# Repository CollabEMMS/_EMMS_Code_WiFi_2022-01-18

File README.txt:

WiFI Module
@author: Zach Holsinger
@editor: Joe Wambach

last edit date: 4/4/2019

v1.0

Version History:
	v1.0: 	Initial Prototype
	v1.1:	Changed Voltage Regulator SCH symbol and footprint
		Changed SPI connector and PICKit connector symbols and footprints

Needs To Be Changed:
	- Pad Size?
	- General Drill Size
	- Need to change holes for 3.3v regulator because holes are too small
		DONE
	- Add silkscreen for DIP switch positions
	- Add silkscreen for SPI header orientation
		DONE
	- Change SCH symbol for headers and connectors
		DONE
	- Add Silkscreen labels to new header footprints
		DONE
	- Add 12V pin on SPI
		DONE

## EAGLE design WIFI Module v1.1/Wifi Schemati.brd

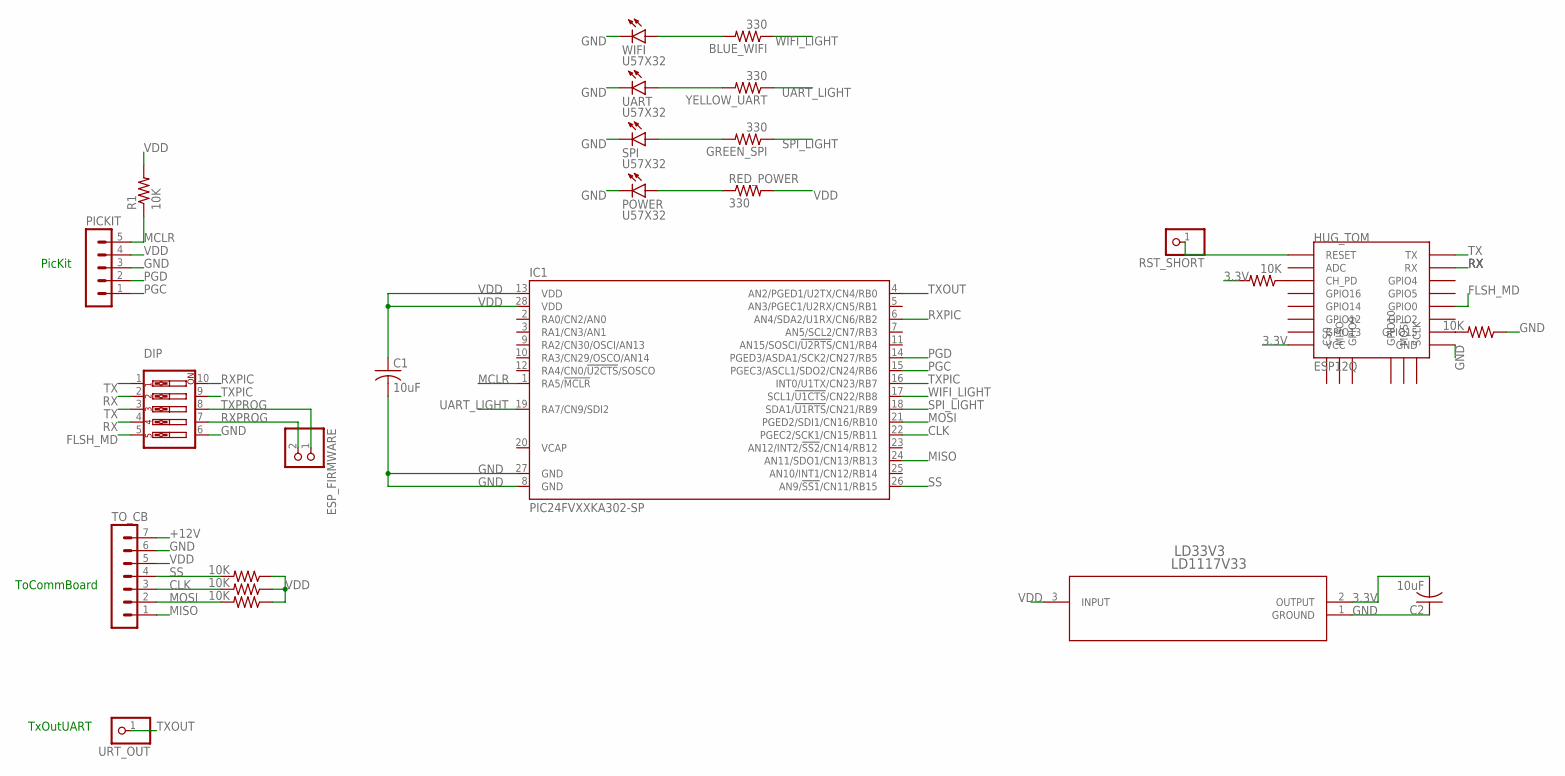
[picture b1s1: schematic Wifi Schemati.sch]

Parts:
BLUE_WIFI: 330; 0207/7
C1, C2: 10uF; C025-025X050
DIP: SW_DIP-5; EDG-05
ESP_FIRMWARE: PINHD-1X2; 1X02
GREEN_SPI: 330; 0207/7
HUG_TOM: ESP12Q
IC1: PIC24FVXXKA302-SP; DIL28-3
LD33V3: LD1117V33; TO-220
PICKIT: MA05-1
POWER: U57X32
R1, R2, R3, R4, R5, R6: 10K; 0207/7
RED_POWER: 330; 0207/7
RST_SHORT: PINHD-1X1; 1X01
SPI: U57X32
TO_CB: MA07-1
UART: U57X32
URT_OUT: PINHD-1X1; 1X01
WIFI: U57X32
YELLOW_UART: 330; 0207/7

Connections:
3.3V: C2.2, HUG_TOM.VCC, LD33V3.2 (OUTPUT), R6.2
+12V: TO_CB.7
CLK: IC1.22 (PGEC2/SCK1/CN15/RB11), R3.2, TO_CB.3
FLSH_MD: DIP.5, HUG_TOM.GPIO0
GND: C1.2, C2.1, DIP.6, HUG_TOM.GND, IC1.8 (GND), IC1.27 (GND), LD33V3.1 (GROUND), PICKIT.3, POWER.K (C), R2.1, SPI.K (C), TO_CB.6, UART.K (C), WIFI.K (C)
MCLR: IC1.1 (RA5/!MCLR), PICKIT.5, R1.1
MISO: IC1.24 (AN11/SDO1/CN13/RB13), TO_CB.1
MOSI: IC1.21 (PGED2/SDI1/CN16/RB10), R4.2, TO_CB.2
unnamed: HUG_TOM.RESET, RST_SHORT.1
unnamed: HUG_TOM.GPIO15, R2.2
unnamed: HUG_TOM.CH_PD, R6.1
unnamed: POWER.A, RED_POWER.1
unnamed: GREEN_SPI.2, SPI.A
unnamed: UART.A, YELLOW_UART.2
unnamed: BLUE_WIFI.2, WIFI.A
PGC: IC1.15 (PGEC3/ASCL1/SDO2/CN24/RB6), PICKIT.1
PGD: IC1.14 (PGED3/ASDA1/SCK2/CN27/RB5), PICKIT.2
RX: DIP.2, DIP.4, HUG_TOM.RX
RXPIC: DIP.10, IC1.6 (AN4/SDA2/U1RX/CN6/RB2)
RXPROG: DIP.7, ESP_FIRMWARE.2
SPI_LIGHT: GREEN_SPI.1, IC1.18 (SDA1/!U1RTS!/CN21/RB9)
SS: IC1.26 (AN9/!SS1!/CN11/RB15), R5.2, TO_CB.4
TX: DIP.1, DIP.3, HUG_TOM.TX
TXOUT: IC1.4 (AN2/PGED1/U2TX/CN4/RB0), URT_OUT.1
TXPIC: DIP.9, IC1.16 (INT0/U1TX/CN23/RB7)
TXPROG: DIP.8, ESP_FIRMWARE.1
UART_LIGHT: IC1.19 (RA7/CN9/SDI2), YELLOW_UART.1
VDD: C1.1, IC1.13 (VDD), IC1.28 (VDD), LD33V3.3 (INPUT), PICKIT.4, R1.2, R3.1, R4.1, R5.1, RED_POWER.2, TO_CB.5
WIFI_LIGHT: BLUE_WIFI.1, IC1.17 (SCL1/!U1CTS!/CN22/RB8)

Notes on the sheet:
ToCommBoard
PicKit
TxOutUART

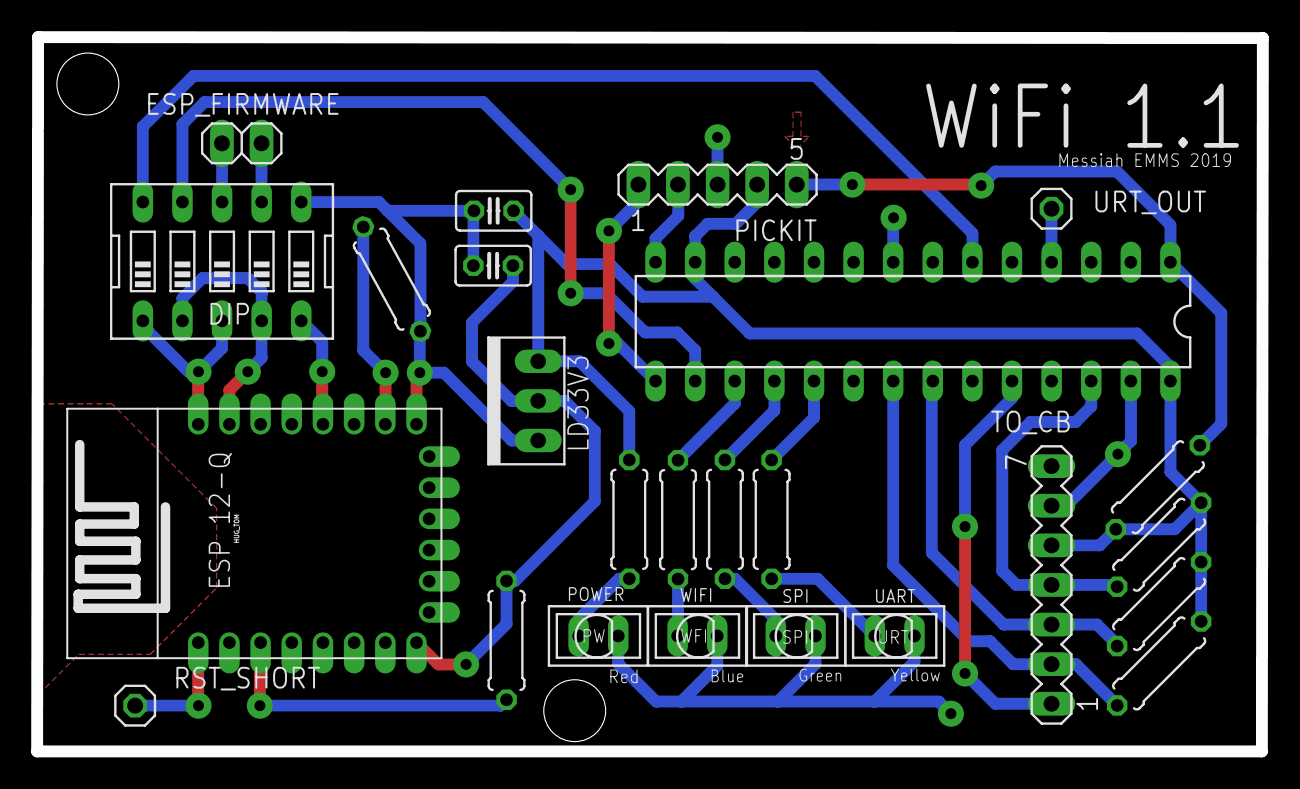
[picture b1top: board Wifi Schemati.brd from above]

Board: 2 copper layers, 78.6 x 45.8 mm, 25 parts (0 on the bottom side), 28 nets.

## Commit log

2017-11-06 :boom::camel: Added .gitattributes
2018-01-25 -CL_WiFi intial version
2019-02-19 Intial Upload - Still Need to Fix SPI Buffer
2019-02-25 Cleaning
    Removed junk, unnessary files not being used. Easier to read
2019-03-07 Added PCB files and README.txt
    Added SCH and PCB files with libraries
    Created README.txt to track changes and list changes to be done
2019-03-09 Update README.txt.txt
    To Do's
2019-03-09 v1.1 and Update README
2019-03-09 v1.1 SCH and PCB update
    Changed SCH and PCB stuff for headers and 3.3v reg
2019-03-11 Update SPI Connector Footprint
2019-03-12 Moving Around Board
    - Rotated ESP 180, fixed reprog issue
2019-03-13 v1.1 PCB Changes
2019-03-13 Changed angle of pull up R's
2019-03-14 Update PCB, 3V3.lbr, and grbs
    Made edits to PCB after milling v1.1
    Updated 3v3.lbr footprint
    Added gerbers from latest mill
2019-03-14 Added mounting holes
2019-03-14 ITS ALIVE
    Currently (Hardware) Working, smaller board. Rev. 1.1
2019-03-14 Gerbers and DRC fixes
2019-03-15 Gerbers take 2
2019-03-15 Gerbers
2019-04-11 BACKDATE PUSH
    - Working UART WIthing Board.
    - Working ESP Basic Setup
    - SPI works for initialization then stops working
2019-04-11 ** FIX AGAIN **
    - Previous Updates, but this time confirmed to work!
2019-04-11 Basic Function Update:
    - Fixed LED Maps
    - Satus Lights actually mean something now
    - Wifi auto-reconnects and reconfigures
    - Found SPI buffer and got '#', so thats good
    - SPI Error seems to be in SPIRBUF in spiCommRecvChar
2019-04-25 Robust Update:
    - WAY MORE Robust autoreconnect w/ error control
    - Added auto print "Messiah College Collaboratory" message to user when properly connected
    - Added get!Config; command to print placeholders for future use
    - Added close command to close the tcp connection from the esp
    - Added reset command which only restarts the wifi init script, hope to restart the whole Pic code in the future.
    - Added failsafe mechanism for multiple SSID's
2019-04-29 Current Update for Tom
    Working on parsing IP from esp
2019-05-07 Fixes
2019-05-07 Function Block Implementation
    Added the functions (at the bottom of the code) to trim the networkData string and also to convert it into something that can be sent through the wifiCommandSet function.
2019-05-07 Minor fix
2019-05-07 Compiling Issues
    Fixed some compiling issues....debating abandoning due to too many changes at once
2019-10-31 African Update
    - Added Changelog so this section is going to be copy paste from now on:
    ==[10/31/2019]==
    MAJOR UPDATE 1
    ================
    African Update:
    - Added Debug Mode
2019-12-10 -- Fixed Emergency Allocation via Button Press (Changed Bit Settings and Double-Checked Comm) -- Added LED pattern to identify button press
2021-04-13 Comments, Comments, Comments!
    Added comments to each function to reduce learning curve for future coders.
2021-09-25 Update WiFi.c
    Added comments in for SSID and password
2021-10-14 Implemented checksum on !Set:Lights command
2021-11-09 added ping/pong command
2021-12-01 meeting dump
